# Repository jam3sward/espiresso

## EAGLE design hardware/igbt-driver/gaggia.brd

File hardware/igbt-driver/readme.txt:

Eagle Schematic and Board files
The CAM files are in the pcb-cam-v1 folder

J.Ward
27/02/15

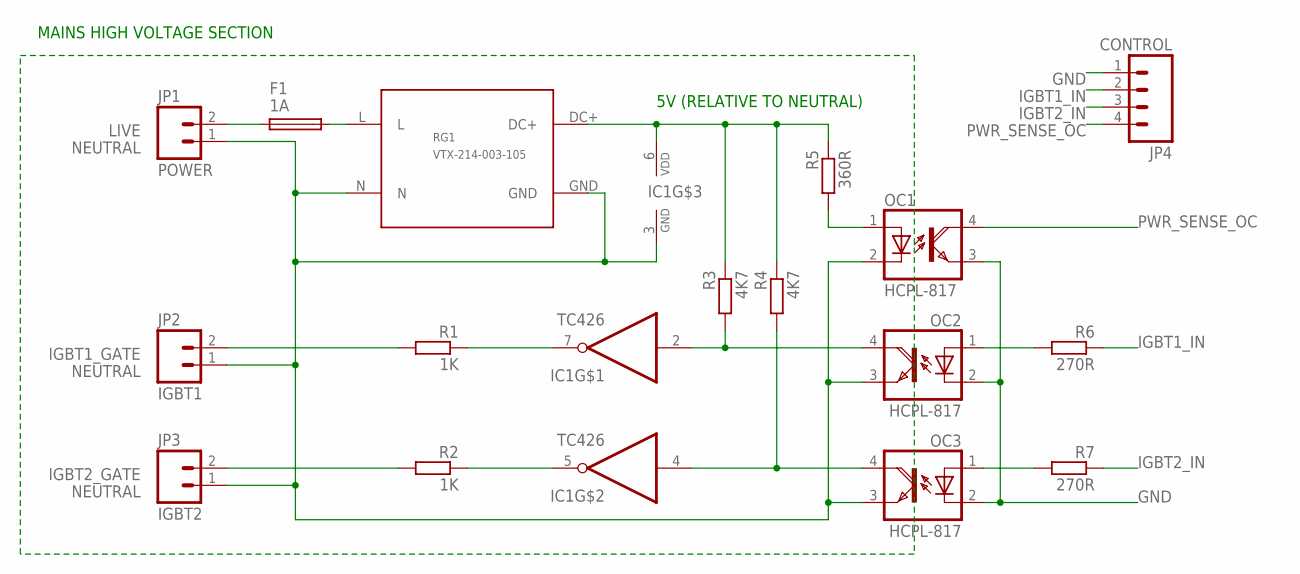
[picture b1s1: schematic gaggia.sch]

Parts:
F1: 1A; TE5
IC1: TC426; DIL08
JP1: POWER; SCREWTERMINAL-5MM-2
JP2: IGBT1; 1X02
JP3: IGBT2; 1X02
JP4: CONTROL; 1X04
OC1, OC2, OC3: HCPL-817; DIL04
R1, R2: 1K; 0204/7
R3, R4: 4K7; 0204/7
R5: 360R; 0204/7
R6, R7: 270R; 0204/7
RG1: VTX-214-003-105; VTX-214-003

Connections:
5V_NON_ISOLATED: IC1.6 (VDD), R3.1, R4.1, R5.1, RG1.DC+
GND: JP4.1, OC1.3 (EMI), OC2.2 (C), OC3.2 (C)
IGBT1_GATE: JP2.2, R1.2
IGBT1_IN: JP4.2, R6.1
IGBT2_GATE: JP3.2, R2.2
IGBT2_IN: JP4.3, R7.1
LIVE: F1.1, JP1.2
unnamed: IC1.4 (I), OC3.4 (COL), R4.2
unnamed: IC1.5 (O), R2.1
unnamed: OC3.1 (A), R7.2
unnamed: IC1.7 (O), R1.1
unnamed: OC1.1 (A), R5.2
unnamed: OC2.1 (A), R6.2
unnamed: IC1.2 (I), OC2.4 (COL), R3.2
unnamed: F1.2, RG1.L
NEUTRAL: IC1.3 (GND), JP1.1, JP2.1, JP3.1, OC1.2 (C), OC2.3 (EMI), OC3.3 (EMI), RG1.GND, RG1.N
PWR_SENSE_OC: JP4.4, OC1.4 (COL)

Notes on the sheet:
MAINS HIGH VOLTAGE SECTION
5V (RELATIVE TO NEUTRAL)

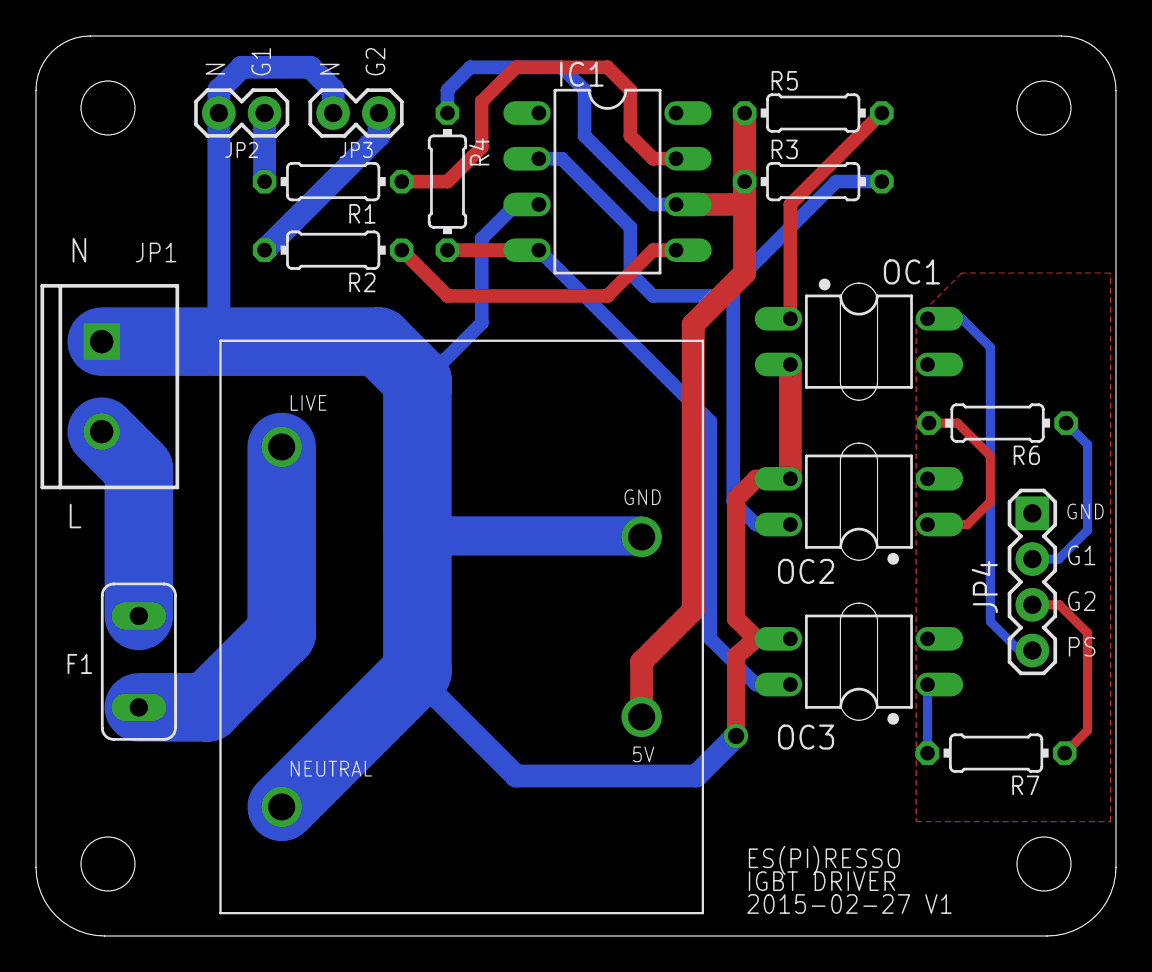
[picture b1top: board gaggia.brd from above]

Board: 2 copper layers, 60.0 x 50.0 mm, 17 parts (0 on the bottom side), 17 nets.

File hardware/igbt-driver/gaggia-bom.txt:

Part Value           Device          Package             Description                              MF MPN OC_FARNELL OC_NEWARK
F1   1A              FUSETE5         TE5                 Fuse                                            unknown    unknown  
IC1  TC426           TC426           DIL08               1.5A Dual High-Speed Power MOSFET Driver                            
JP1  POWER           M025MM          SCREWTERMINAL-5MM-2 Standard 2-pin 0.1" header.                             
JP2  IGBT1           M02PTH          1X02                Standard 2-pin 0.1" header.                               
JP3  IGBT2           M02PTH          1X02                Standard 2-pin 0.1" header.                               
JP4  CONTROL         M04PTH          1X04                Standard 4-pin 0.1" header.                                                       
OC1  HCPL-817        TIL197          DIL04               TEXAS INSTRUMENTS OPTO COUPLER                  1683368    unknown  
OC2  HCPL-817        TIL197          DIL04               TEXAS INSTRUMENTS OPTO COUPLER                  1683368    unknown  
OC3  HCPL-817        TIL197          DIL04               TEXAS INSTRUMENTS OPTO COUPLER                  1683368    unknown  
R1   1K              R-EU_0204/7     0204/7              RESISTOR                                          
R2   1K              R-EU_0204/7     0204/7              RESISTOR                                         
R3   4K7             R-EU_0204/7     0204/7              RESISTOR                                           
R4   4K7             R-EU_0204/7     0204/7              RESISTOR                                           
R5   360R            R-EU_0204/7     0204/7              RESISTOR                                           
R6   270R            R-EU_0204/7     0204/7              RESISTOR                                           
R7   270R            R-EU_0204/7     0204/7              RESISTOR                                           
RG1  VTX-214-003-105 VTX-214-003-105 VTX-214-003         Vigortronix 90-265V AC to 5V DC 600mA

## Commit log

2012-12-26 created trunk folder
2013-05-28 First import of Gaggia PID temperature controller for Raspberry Pi
2013-05-28 Modified getClock() to use clock_gettime() in order to avoid jumps due to NTP and other time adjustments.
2013-06-01 Changed PID parameters, added interactive mode and altered number of decimal places in output files.
2013-10-31 Modified to use hardware PWM, as yet untested.
2013-10-31 Added missing PWM files (forgot to commit previously)
2013-10-31 Added inputs class for halt button
2013-11-02 Fixed bug with improper boiler shutdown.
2013-11-02 Fixed SSR pin assignment used for hardware PWM. Added comments and assertion for documentation purposes.
2013-11-02 Settings are now read from a configuration file (sample file committed here) Added readme file with some more documentation
2013-11-23 Added GPIOPin class which uses the sysfs GPIO interface.
2013-11-23 Added Ranger class which implements support for the Ultrasonic Ranger Finder.
2013-11-23 Updated Makefile to incorporate new files.
2013-12-10 Additional code to disable PWM
2013-12-10 Added up to date pinout
2013-12-11 Implemented an interface class for the water flow sensor. Tested and apparently working.
2013-12-11 Flow sensor can now measure in litres. Performed basic calibration using digital scales with the sensor in situ on the Gaggia machine.
2013-12-11 Added comments with manufacturer/model/specification of the flow sensor.
2013-12-11 Modified to output the flow volume (ml) to the log.
2013-12-12 Added functions to check that Flow meter IO was successfully initialised.
2013-12-13 The flow sensor can now send an asynchronous notification when a specified volume of water has been pumped.
2013-12-13 Modified comments.
2014-02-11 Modified GPIO pins for new hardware. Removed references to halt button. Added new system class which allows core temperature to be queried. Added test mode which displays sensor data.
2014-02-11 Modified sensor test mode to display units, and range in mm.
2014-02-11 Modified Ranger to sample on separate thread, to avoid blocking. It attempts to remove outliers (with limited success) and low pass filters data.
2014-02-11 Adjusted Ranger minimum interval to 0.25s to try and reduce range errors.
2014-02-11 Added control of Pump (press P key during test mode to toggle on/off).
2014-02-11 Added support for button inputs (not yet working, assumed due to clash with BCM IO functions).
2014-02-12 Fixed a bug with missing call to BCM::open() in PWM ctor. Rewrote Temperature class to use w1-therm module. Fixed a bug in GPIOPin::getState() which failed to rewind file before reading.
2014-02-16 Added current boiler temperature display to LCD.
2014-02-16 Added basic water level indication (doesn't work all that well). Added graceful shutdown on receipt of SIGINT and SIGTERM.
2014-02-16 Temporarily added halt function on button 1.
2014-02-16 Forgot to add Display previously.
2014-02-20 Extended Flow class to send notifications when flow starts, stops or reaches target volume. Added simple code to gaggia.cpp to test this new functionality.
2014-02-28 Updated pinout
2014-02-28 Started refactoring temperature control loop into a separate Regulator class. This will eventually allow the user interface thread to run independently.
2014-03-01 Refactored to use the new Regulator class to manage temperature. Added methods to Regulator to read current boiler power level.
2014-04-14 Added new TSIC 306 sensor to pinout
2014-04-14 Added safety check in case of zero temperature sensor reading
2014-04-20 Modified range finder to use HC-SR04 kernel module instead of polling the sensor from user mode.
2014-04-21 Now using TSIC 306 temperature sensor, via kernel driver.
2014-04-21 Water level indicator now uses 20-100mm range, based on measurements in situ. Pump test function now dispenses 60ml. Added range test which reports an average of 50 readings. Introduced 250ms delay i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
2014-04-21 Added getPower method to Regulator class.
2014-04-21 Added notification callback to Inputs class.
2014-04-21 Makefile updated for inputs.cpp
2014-04-21 Button 1 now dispenses a measured shot, using the flow sensor. The pump can be stopped by a second button push. Pressing button 2 briefly toggles the boiler power. Pressing button 2 for 1 second shut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
2014-04-24 Added missing mutex to inputs.h and inputs.cpp
2014-04-29 Added safe mode: if button 2 is held during start up, the controller will exit. This is useful when you want to SSH into the machine without starting up the boiler.
2014-04-30 Modified test loop to sample on a more regular time step.
2014-04-30 Increased poll timeout for flow sensor to 1 second, to reduce overhead. Fixed bug with pump being turned off in test loop.
2014-07-14 Added automatic power off function, to shut down the boiler if the machine is left for a long period without any user input. This is configured with the autoPowerOff setting in the configuration file.
2014-07-19 Reset the g_lastUsed timer when the pump is used via the front panel switch.
2014-07-19 Fixed warnings which appeared after installing SDL image (type narrowing from signed to unsigned short)
2015-01-03 Added preliminary code to interface with ADS1015 ADC. This has been tested separately but not yet integrated.
2015-01-03 The ADC is now used to read the state of both front panel buttons through a single analogue input, using a resistor ladder.
2015-01-04 Automatically close the ADC at destruction.
2015-01-04 Added user mode driver for HSCR-04 range finder, using PIGPIO.
2015-01-04 Added TSIC GPIO pin to settings.h
2015-01-04 Modified Temperature class to use user mode driver via PIGPIO
2015-01-04 Added PIGPIOManager class to manage initialisation of PIGPIO
2015-01-04 Modified Ranger class to use HCSR04 class instead of kernel mode driver
2015-01-04 Added TSIC 306 user mode driver using PIGPIOD via pigpiod_if
2015-01-06 Modified to use PIGPIOD for the majority of the GPIO. Moved static variables into class. Partially tested and working in test mode (not yet tested controller or PWM). Temperature, Ranger, Flow sensor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
2015-01-06 Added code to install the button and flow notification handlers.
2015-01-09 Added support for pressure sensor. Although not yet calibrated, it seems reasonably consistent with the front panel pressure gauge.
2015-01-11 Added a mutex to ADC::getVoltage to allow simultaneous access from the threads used to process button inputs (Input) and pressure sensor readings (Pressure). Modified GPIOPin class to return the last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
2015-01-11 Added Raspberry Pi device tree source file from August 1st 2014 firmware, with the idea of modifying this to set the initial power up state of the GPIO pins.
2015-01-11 Configured pump GPIO pins as inputs with pull-down at boot time, to prevent it being enabled as the system boots.
2015-01-11 Made the pump PWM duty default to 100% to allow manual use of the machine without pump modulation. Added test code for the brew switch power detect (working!) Added logging of pressure sensor measure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
2015-01-12 Added pressure output to console in interactive controller mode.
2015-01-12 Fixed typo in comment
2015-01-12 Fixed a bug with reporting flow start/stop events, due to incorrect timeout introduced when the code was changed to use PIGPIO.
2015-01-12 Changed flow pulse counter to use atomic unsigned long
2015-01-12 Added code to test pump PWM modulation (it works!)
2015-01-17 More rigorous checking of pulse widths for TSIC temperature sensor, and pull up configuration, in an attempt to improve robustness against spikes.
2015-01-17 Added pull up/down configuration to GPIOPin class
2015-01-17 Added pressure display on LCD.
2015-01-24 Added an icon to show when boiler power is enabled.
2015-01-24 Added new icon for boiler power (not yet used)
2015-01-24 Made boiler icon configurable
2015-01-24 Added pump icon
2015-01-24 Added pump icon to indicate when the pump power is on.
2015-01-24 Now keeps track of the number of times the pump has been run (pours)
2015-01-29 Fixed bug with TSIC code. Increased timing tolerance in an attempt to improve robustness. Renamed variables to make code more comprehensible.
2015-01-29 Use an average of 3 ADC samples for pressure sensor readings, to compensate for jitter due to EP5 vibration pump.
2015-03-10 Added some instructions on how to compile the device tree source
2015-03-10 Added shot timer, which displays elapsed time in seconds during a shot. Currently based on pump power sense output (therefore runs on slightly).
2015-06-07 Added pressure transducer calibration (scale and offset). These can be used to adjust the analogue pressure sensor readings to match the mechanical pressure gauge.
2015-12-12 Aded includes to fix compilation issues after OS upgrade
2015-12-28 Added startup scripts, missing from original commit (but used on my machine)
2015-12-29 Added device tree overlay to ensure GPIO pins used by pump are low at first boot
2015-12-29 Added an updated dt-blob.dts (original Raspberry Pi version), prior to making the required changes, which I'll do in a second commit.
2015-12-29 Changes to ensure that GPIO 14 and 15 used by the pump are low on first boot
2015-12-29 Added Makefile to compile the dt-blob.dts to binary blob
2015-12-29 Changed halt to poweroff (fix issue with not powering down since update of Raspbian)
2015-12-29 Added install function to Makefile
2015-12-29 Started adding hardware and PCB design files
2015-12-29 Added bill of materials
2020-11-16 Power off now occurs after process exit, allowing shutdown messages to be viewed on console.
2020-11-20 Display the primary IP address on the LCD
2020-11-20 Allow time for network to connect before displaying IP
2021-11-11 Fixed warning due to missing return
2021-11-11 Updated dt-blob.dts for latest Raspberry Pi variants
2021-11-13 Ignore SIGHUP to allow this to run as a systemd service

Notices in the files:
parts and their libraries:
SparkFun-Connectors: Licensing: CC v3.0 Share-Alike You are welcome to use this library for commercial purposes.
